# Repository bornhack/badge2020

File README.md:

# Bornhack Badge 2020

## About the hardware

Similar to the last couple of years, this badge has an ARM cortex M0+ as the main
controller, but on this badge it's the SAMD21 from Microchip, with 4 times as much
flash and RAM compared to the chips from the previous badges.

This makes it possible to run Adafruit CircuitPython on this badge, which lowers the
bar for how easy it is to get started hacking on the badge, since all you need is a
USB cable to connect it to your computer and an editor (vi, nano, VSCode, notepad,
you name it) to change the `code.py` file on the badge. No need to have a tool chain
installed on your computer, it's all happening on the badge when you save the file.

## Features

- The main feature of the badge is a 9x32 pixel LED matrix controlled by 2
IS31FL3731 LED controllers, that control the LEDs via charlieplexing
- The other primary feature is an infrared LED to transmit and an infrared receiver
and decoder to receive badge to badge communication
- There are also 4 navigation/game buttons and a reset button
- The badge is either powered by 2xAA batteries, that have the voltage boosted to
3.3v or via USB, where the voltage is regulated down to 3.3v
- The main controller is a SAMD21G18A with a GD25Q32C (4MB SPI flash) connected
for libraries, graphics, etc.
- There is also an unpopulated header for Shitty Add On v.1.69bis
- On the back of the badge, all i/o pins that are not used on the microcontroller
is pull out to small SMD pads for optional soldering on add-ons or similar.

## Getting started

To start making your badge your own, you can connect it via USB and a mass storage
device should show up with a `code.py` file in the root directory.

If you open that file in your favorite text editor you will find a few lines first
that loads some libraries, then some initialisation of the LED drivers and on line 20
you will find an assignment of a string variable with the scrolling text shown on
the LED matrix. To put eg. your name on the badge, you can change this text and save
the file, and after a few seconds, the badge will restart the code and your text
should be slowly scrolling across the "screen".

If you have gotten this far you are up and running with your first "hack" of the
2020 BornHack badge and you can continue with more elaborate hacking.

## Projects using the badge

- [Generative animations in OCaml](https://github.com/rand00/bornhack2020-badge_generative-animations)
  - Animations are pregenerated in OCaml and played back on the badge using python

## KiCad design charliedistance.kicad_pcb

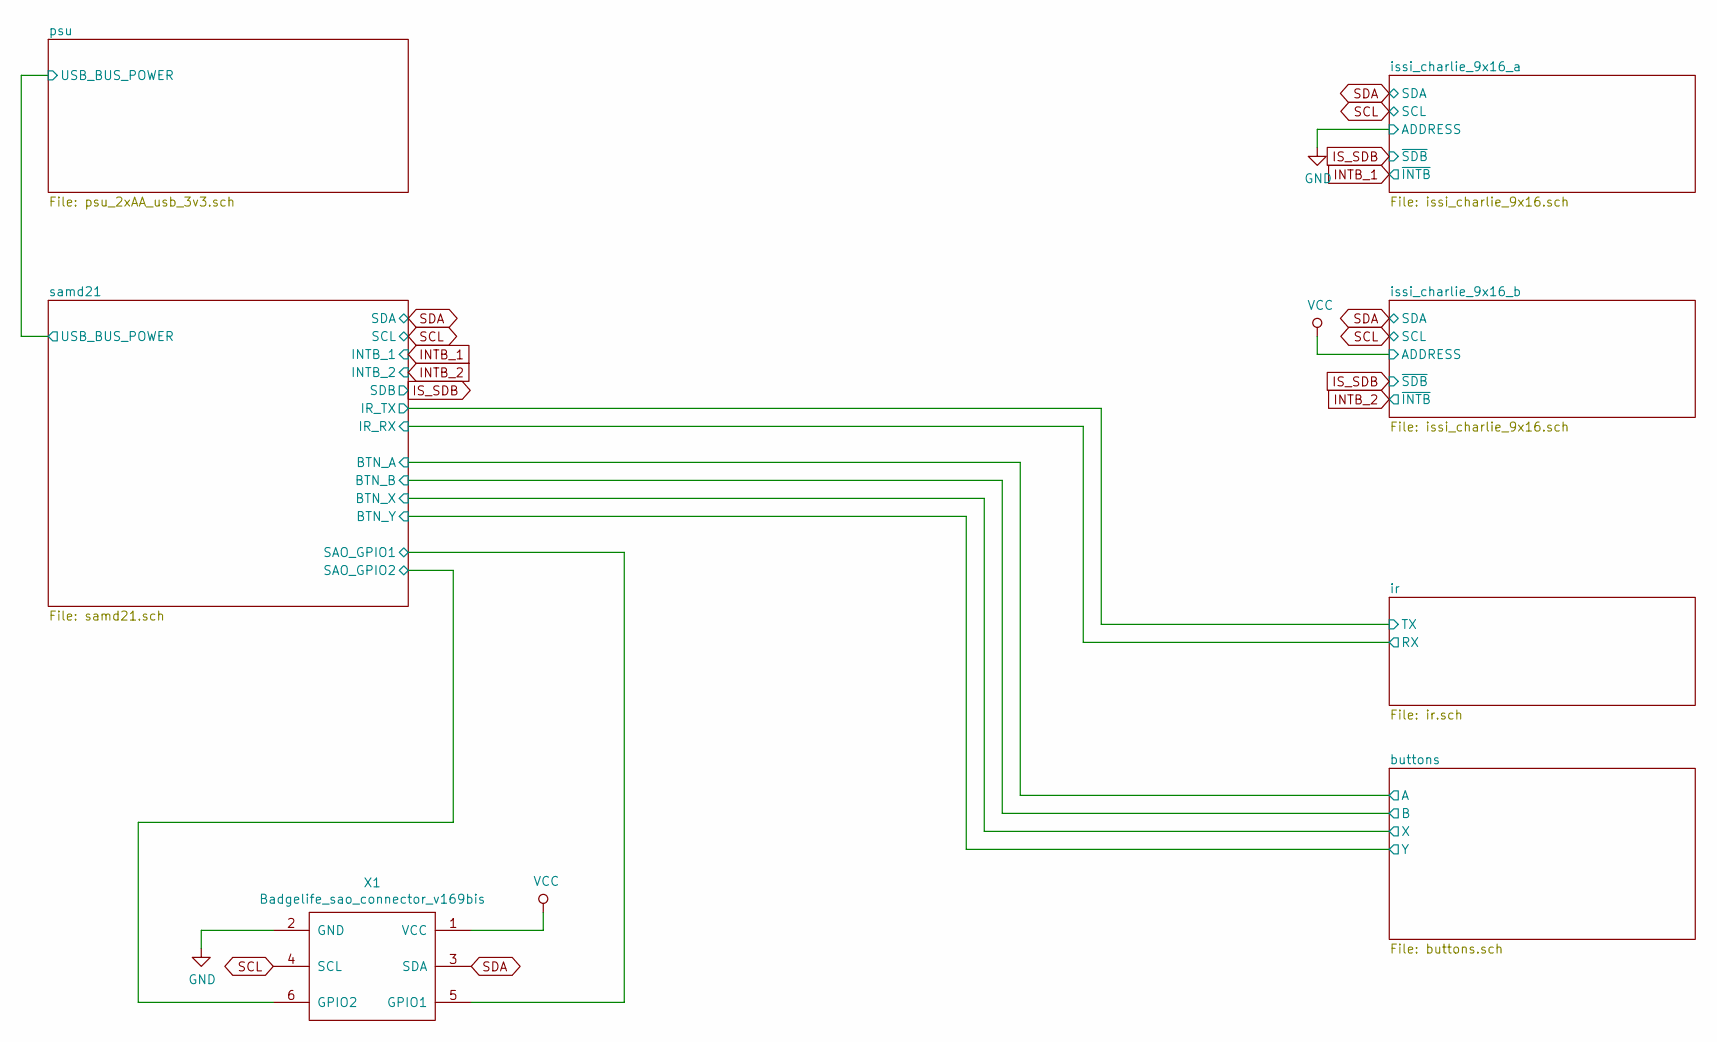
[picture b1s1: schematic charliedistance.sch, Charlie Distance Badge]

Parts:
X1: Badgelife_sao_connector_v169bis; Badgelife-SAOv169-BADGE-2x3

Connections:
/samd21/SAO_GPIO1: X1.5 (GPIO1); also elsewhere on the board
/samd21/SAO_GPIO2: X1.6 (GPIO2); also elsewhere on the board
GND: X1.2 (GND); also elsewhere on the board
SCL: X1.4 (SCL); also elsewhere on the board
SDA: X1.3 (SDA); also elsewhere on the board
VCC: X1.1 (VCC); also elsewhere on the board

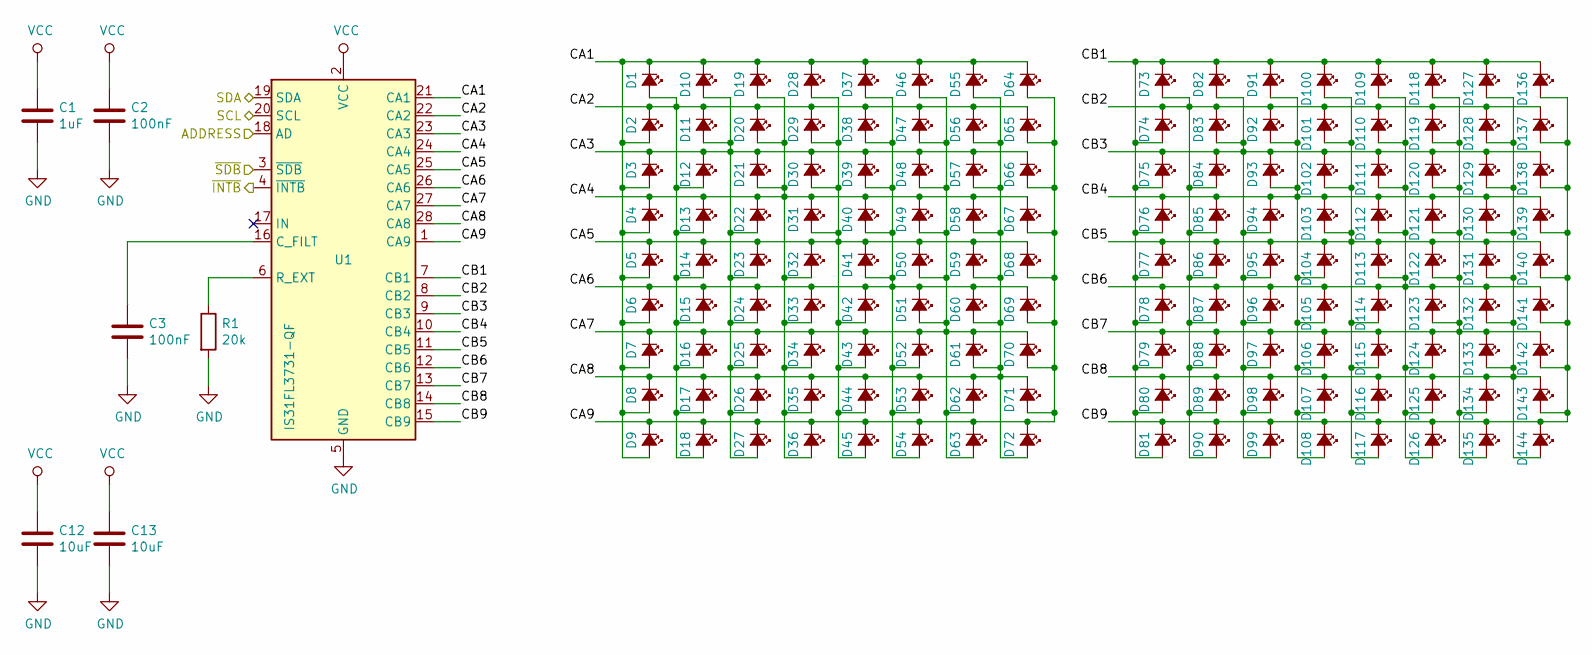
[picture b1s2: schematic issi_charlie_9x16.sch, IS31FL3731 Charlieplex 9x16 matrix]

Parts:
C1: 1uF; C_0603
C2, C3: 100nF; C_0603
C12, C13: 10uF; C_0603
D1, D2, D3, D4, D5, D6, D7, D8, D9, D10, D11, D12, D13, D14, D15, D16, D17, D18, D19, D20, D21, D22, D23, D24, D25, D26, D27, D28, D29, D30, D31, D32, D33, D34, D35, D36, D37, D38, D39, D40, D41, D42, D43, D44, D45, D46, D47, D48, D49, D50, D51, D52, D53, D54, D55, D56, D57, D58, D59, D60, D61, D62, D63, D64, D65, D66, D67, D68, D69, D70, D71, D72, D73, D74, D75, D76, D77, D78, D79, D80, D81, D82, D83, D84, D85, D86, D87, D88, D89, D90, D91, D92, D93, D94, D95, D96, D97, D98, D99, D100, D101, D102, D103, D104, D105, D106, D107, D108, D109, D110, D111, D112, D113, D114, D115, D116, D117, D118, D119, D120, D121, D122, D123, D124, D125, D126, D127, D128, D129, D130, D131, D132, D133, D134, D135, D136, D137, D138, D139, D140, D141, D142, D143, D144: LED_Small_ALT; LED_0603
R1: 20k; R_0603
U1: IS31FL3731-QF; QFN-28-1EP_4x4mm_Pitch0.4mm

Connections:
/issi_charlie_9x16_a/CA1: D1.1 (K), D2.2 (A), D3.2 (A), D4.2 (A), D5.2 (A), D6.2 (A), D7.2 (A), D8.2 (A), D9.2 (A), D10.1 (K), D19.1 (K), D28.1 (K), D37.1 (K), D46.1 (K), D55.1 (K), D64.1 (K), U1.21 (CA1)
/issi_charlie_9x16_a/CA2: D1.2 (A), D2.1 (K), D11.1 (K), D12.2 (A), D13.2 (A), D14.2 (A), D15.2 (A), D16.2 (A), D17.2 (A), D18.2 (A), D20.1 (K), D29.1 (K), D38.1 (K), D47.1 (K), D56.1 (K), D65.1 (K), U1.22 (CA2)
/issi_charlie_9x16_a/CA3: D3.1 (K), D10.2 (A), D11.2 (A), D12.1 (K), D21.1 (K), D22.2 (A), D23.2 (A), D24.2 (A), D25.2 (A), D26.2 (A), D27.2 (A), D30.1 (K), D39.1 (K), D48.1 (K), D57.1 (K), D66.1 (K), U1.23 (CA3)
/issi_charlie_9x16_a/CA4: D4.1 (K), D13.1 (K), D19.2 (A), D20.2 (A), D21.2 (A), D22.1 (K), D31.1 (K), D32.2 (A), D33.2 (A), D34.2 (A), D35.2 (A), D36.2 (A), D40.1 (K), D49.1 (K), D58.1 (K), D67.1 (K), U1.24 (CA4)
/issi_charlie_9x16_a/CA5: D5.1 (K), D14.1 (K), D23.1 (K), D28.2 (A), D29.2 (A), D30.2 (A), D31.2 (A), D32.1 (K), D41.1 (K), D42.2 (A), D43.2 (A), D44.2 (A), D45.2 (A), D50.1 (K), D59.1 (K), D68.1 (K), U1.25 (CA5)
/issi_charlie_9x16_a/CA6: D6.1 (K), D15.1 (K), D24.1 (K), D33.1 (K), D37.2 (A), D38.2 (A), D39.2 (A), D40.2 (A), D41.2 (A), D42.1 (K), D51.1 (K), D52.2 (A), D53.2 (A), D54.2 (A), D60.1 (K), D69.1 (K), U1.26 (CA6)
/issi_charlie_9x16_a/CA7: D7.1 (K), D16.1 (K), D25.1 (K), D34.1 (K), D43.1 (K), D46.2 (A), D47.2 (A), D48.2 (A), D49.2 (A), D50.2 (A), D51.2 (A), D52.1 (K), D61.1 (K), D62.2 (A), D63.2 (A), D70.1 (K), U1.27 (CA7)
/issi_charlie_9x16_a/CA8: D8.1 (K), D17.1 (K), D26.1 (K), D35.1 (K), D44.1 (K), D53.1 (K), D55.2 (A), D56.2 (A), D57.2 (A), D58.2 (A), D59.2 (A), D60.2 (A), D61.2 (A), D62.1 (K), D71.1 (K), D72.2 (A), U1.28 (CA8)
/issi_charlie_9x16_a/CA9: D9.1 (K), D18.1 (K), D27.1 (K), D36.1 (K), D45.1 (K), D54.1 (K), D63.1 (K), D64.2 (A), D65.2 (A), D66.2 (A), D67.2 (A), D68.2 (A), D69.2 (A), D70.2 (A), D71.2 (A), D72.1 (K), U1.1 (CA9)
/issi_charlie_9x16_a/CB1: D73.1 (K), D74.2 (A), D75.2 (A), D76.2 (A), D77.2 (A), D78.2 (A), D79.2 (A), D80.2 (A), D81.2 (A), D82.1 (K), D91.1 (K), D100.1 (K), D109.1 (K), D118.1 (K), D127.1 (K), D136.1 (K), U1.7 (CB1)
/issi_charlie_9x16_a/CB2: D73.2 (A), D74.1 (K), D83.1 (K), D84.2 (A), D85.2 (A), D86.2 (A), D87.2 (A), D88.2 (A), D89.2 (A), D90.2 (A), D92.1 (K), D101.1 (K), D110.1 (K), D119.1 (K), D128.1 (K), D137.1 (K), U1.8 (CB2)
/issi_charlie_9x16_a/CB3: D75.1 (K), D82.2 (A), D83.2 (A), D84.1 (K), D93.1 (K), D94.2 (A), D95.2 (A), D96.2 (A), D97.2 (A), D98.2 (A), D99.2 (A), D102.1 (K), D111.1 (K), D120.1 (K), D129.1 (K), D138.1 (K), U1.9 (CB3)
/issi_charlie_9x16_a/CB4: D76.1 (K), D85.1 (K), D91.2 (A), D92.2 (A), D93.2 (A), D94.1 (K), D103.1 (K), D104.2 (A), D105.2 (A), D106.2 (A), D107.2 (A), D108.2 (A), D112.1 (K), D121.1 (K), D130.1 (K), D139.1 (K), U1.10 (CB4)
/issi_charlie_9x16_a/CB5: D77.1 (K), D86.1 (K), D95.1 (K), D100.2 (A), D101.2 (A), D102.2 (A), D103.2 (A), D104.1 (K), D113.1 (K), D114.2 (A), D115.2 (A), D116.2 (A), D117.2 (A), D122.1 (K), D131.1 (K), D140.1 (K), U1.11 (CB5)
/issi_charlie_9x16_a/CB6: D78.1 (K), D87.1 (K), D96.1 (K), D105.1 (K), D109.2 (A), D110.2 (A), D111.2 (A), D112.2 (A), D113.2 (A), D114.1 (K), D123.1 (K), D124.2 (A), D125.2 (A), D126.2 (A), D132.1 (K), D141.1 (K), U1.12 (CB6)
/issi_charlie_9x16_a/CB7: D79.1 (K), D88.1 (K), D97.1 (K), D106.1 (K), D115.1 (K), D118.2 (A), D119.2 (A), D120.2 (A), D121.2 (A), D122.2 (A), D123.2 (A), D124.1 (K), D133.1 (K), D134.2 (A), D135.2 (A), D142.1 (K), U1.13 (CB7)
/issi_charlie_9x16_a/CB8: D80.1 (K), D89.1 (K), D98.1 (K), D107.1 (K), D116.1 (K), D125.1 (K), D127.2 (A), D128.2 (A), D129.2 (A), D130.2 (A), D131.2 (A), D132.2 (A), D133.2 (A), D134.1 (K), D143.1 (K), D144.2 (A), U1.14 (CB8)
/issi_charlie_9x16_a/CB9: D81.1 (K), D90.1 (K), D99.1 (K), D108.1 (K), D117.1 (K), D126.1 (K), D135.1 (K), D136.2 (A), D137.2 (A), D138.2 (A), D139.2 (A), D140.2 (A), D141.2 (A), D142.2 (A), D143.2 (A), D144.1 (K), U1.15 (CB9)
GND: C1.2, C2.2, C3.2, C12.2, C13.2, R1.2, U1.5 (GND), U1.18 (AD), U1.29 (GND); also elsewhere on the board
INTB_1: U1.4 (~INTB); also elsewhere on the board
IS_SDB: U1.3 (~SDB); also elsewhere on the board
unnamed: C3.1, U1.16 (C_FILT)
unnamed: R1.1, U1.6 (R_EXT)
SCL: U1.20 (SCL); also elsewhere on the board
SDA: U1.19 (SDA); also elsewhere on the board
VCC: C1.1, C2.1, C12.1, C13.1, U1.2 (VCC); also elsewhere on the board

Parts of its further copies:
C4: 1uF; C_0603
C5, C6: 100nF; C_0603
C14, C15: 10uF; C_0603
D145, D146, D147, D148, D149, D150, D151, D152, D153, D154, D155, D156, D157, D158, D159, D160, D161, D162, D163, D164, D165, D166, D167, D168, D169, D170, D171, D172, D173, D174, D175, D176, D177, D178, D179, D180, D181, D182, D183, D184, D185, D186, D187, D188, D189, D190, D191, D192, D193, D194, D195, D196, D197, D198, D199, D200, D201, D202, D203, D204, D205, D206, D207, D208, D209, D210, D211, D212, D213, D214, D215, D216, D217, D218, D219, D220, D221, D222, D223, D224, D225, D226, D227, D228, D229, D230, D231, D232, D233, D234, D235, D236, D237, D238, D239, D240, D241, D242, D243, D244, D245, D246, D247, D248, D249, D250, D251, D252, D253, D254, D255, D256, D257, D258, D259, D260, D261, D262, D263, D264, D265, D266, D267, D268, D269, D270, D271, D272, D273, D274, D275, D276, D277, D278, D279, D280, D281, D282, D283, D284, D285, D286, D287, D288: LED_Small_ALT; LED_0603
R2: 20k; R_0603
U2: IS31FL3731-QF; QFN-28-1EP_4x4mm_Pitch0.4mm

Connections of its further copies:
/issi_charlie_9x16_b/CA1: D145.1 (K), D146.2 (A), D147.2 (A), D148.2 (A), D149.2 (A), D150.2 (A), D151.2 (A), D152.2 (A), D153.2 (A), D154.1 (K), D163.1 (K), D172.1 (K), D181.1 (K), D190.1 (K), D199.1 (K), D208.1 (K), U2.21 (CA1)
/issi_charlie_9x16_b/CA2: D145.2 (A), D146.1 (K), D155.1 (K), D156.2 (A), D157.2 (A), D158.2 (A), D159.2 (A), D160.2 (A), D161.2 (A), D162.2 (A), D164.1 (K), D173.1 (K), D182.1 (K), D191.1 (K), D200.1 (K), D209.1 (K), U2.22 (CA2)
/issi_charlie_9x16_b/CA3: D147.1 (K), D154.2 (A), D155.2 (A), D156.1 (K), D165.1 (K), D166.2 (A), D167.2 (A), D168.2 (A), D169.2 (A), D170.2 (A), D171.2 (A), D174.1 (K), D183.1 (K), D192.1 (K), D201.1 (K), D210.1 (K), U2.23 (CA3)
/issi_charlie_9x16_b/CA4: D148.1 (K), D157.1 (K), D163.2 (A), D164.2 (A), D165.2 (A), D166.1 (K), D175.1 (K), D176.2 (A), D177.2 (A), D178.2 (A), D179.2 (A), D180.2 (A), D184.1 (K), D193.1 (K), D202.1 (K), D211.1 (K), U2.24 (CA4)
/issi_charlie_9x16_b/CA5: D149.1 (K), D158.1 (K), D167.1 (K), D172.2 (A), D173.2 (A), D174.2 (A), D175.2 (A), D176.1 (K), D185.1 (K), D186.2 (A), D187.2 (A), D188.2 (A), D189.2 (A), D194.1 (K), D203.1 (K), D212.1 (K), U2.25 (CA5)
/issi_charlie_9x16_b/CA6: D150.1 (K), D159.1 (K), D168.1 (K), D177.1 (K), D181.2 (A), D182.2 (A), D183.2 (A), D184.2 (A), D185.2 (A), D186.1 (K), D195.1 (K), D196.2 (A), D197.2 (A), D198.2 (A), D204.1 (K), D213.1 (K), U2.26 (CA6)
/issi_charlie_9x16_b/CA7: D151.1 (K), D160.1 (K), D169.1 (K), D178.1 (K), D187.1 (K), D190.2 (A), D191.2 (A), D192.2 (A), D193.2 (A), D194.2 (A), D195.2 (A), D196.1 (K), D205.1 (K), D206.2 (A), D207.2 (A), D214.1 (K), U2.27 (CA7)
/issi_charlie_9x16_b/CA8: D152.1 (K), D161.1 (K), D170.1 (K), D179.1 (K), D188.1 (K), D197.1 (K), D199.2 (A), D200.2 (A), D201.2 (A), D202.2 (A), D203.2 (A), D204.2 (A), D205.2 (A), D206.1 (K), D215.1 (K), D216.2 (A), U2.28 (CA8)
/issi_charlie_9x16_b/CA9: D153.1 (K), D162.1 (K), D171.1 (K), D180.1 (K), D189.1 (K), D198.1 (K), D207.1 (K), D208.2 (A), D209.2 (A), D210.2 (A), D211.2 (A), D212.2 (A), D213.2 (A), D214.2 (A), D215.2 (A), D216.1 (K), U2.1 (CA9)
/issi_charlie_9x16_b/CB1: D217.1 (K), D218.2 (A), D219.2 (A), D220.2 (A), D221.2 (A), D222.2 (A), D223.2 (A), D224.2 (A), D225.2 (A), D226.1 (K), D235.1 (K), D244.1 (K), D253.1 (K), D262.1 (K), D271.1 (K), D280.1 (K), U2.7 (CB1)
/issi_charlie_9x16_b/CB2: D217.2 (A), D218.1 (K), D227.1 (K), D228.2 (A), D229.2 (A), D230.2 (A), D231.2 (A), D232.2 (A), D233.2 (A), D234.2 (A), D236.1 (K), D245.1 (K), D254.1 (K), D263.1 (K), D272.1 (K), D281.1 (K), U2.8 (CB2)
/issi_charlie_9x16_b/CB3: D219.1 (K), D226.2 (A), D227.2 (A), D228.1 (K), D237.1 (K), D238.2 (A), D239.2 (A), D240.2 (A), D241.2 (A), D242.2 (A), D243.2 (A), D246.1 (K), D255.1 (K), D264.1 (K), D273.1 (K), D282.1 (K), U2.9 (CB3)
/issi_charlie_9x16_b/CB4: D220.1 (K), D229.1 (K), D235.2 (A), D236.2 (A), D237.2 (A), D238.1 (K), D247.1 (K), D248.2 (A), D249.2 (A), D250.2 (A), D251.2 (A), D252.2 (A), D256.1 (K), D265.1 (K), D274.1 (K), D283.1 (K), U2.10 (CB4)
/issi_charlie_9x16_b/CB5: D221.1 (K), D230.1 (K), D239.1 (K), D244.2 (A), D245.2 (A), D246.2 (A), D247.2 (A), D248.1 (K), D257.1 (K), D258.2 (A), D259.2 (A), D260.2 (A), D261.2 (A), D266.1 (K), D275.1 (K), D284.1 (K), U2.11 (CB5)
/issi_charlie_9x16_b/CB6: D222.1 (K), D231.1 (K), D240.1 (K), D249.1 (K), D253.2 (A), D254.2 (A), D255.2 (A), D256.2 (A), D257.2 (A), D258.1 (K), D267.1 (K), D268.2 (A), D269.2 (A), D270.2 (A), D276.1 (K), D285.1 (K), U2.12 (CB6)
/issi_charlie_9x16_b/CB7: D223.1 (K), D232.1 (K), D241.1 (K), D250.1 (K), D259.1 (K), D262.2 (A), D263.2 (A), D264.2 (A), D265.2 (A), D266.2 (A), D267.2 (A), D268.1 (K), D277.1 (K), D278.2 (A), D279.2 (A), D286.1 (K), U2.13 (CB7)
/issi_charlie_9x16_b/CB8: D224.1 (K), D233.1 (K), D242.1 (K), D251.1 (K), D260.1 (K), D269.1 (K), D271.2 (A), D272.2 (A), D273.2 (A), D274.2 (A), D275.2 (A), D276.2 (A), D277.2 (A), D278.1 (K), D287.1 (K), D288.2 (A), U2.14 (CB8)
/issi_charlie_9x16_b/CB9: D225.1 (K), D234.1 (K), D243.1 (K), D252.1 (K), D261.1 (K), D270.1 (K), D279.1 (K), D280.2 (A), D281.2 (A), D282.2 (A), D283.2 (A), D284.2 (A), D285.2 (A), D286.2 (A), D287.2 (A), D288.1 (K), U2.15 (CB9)
GND: C4.2, C5.2, C6.2, C14.2, C15.2, R2.2, U2.5 (GND), U2.29 (GND); also elsewhere on the board
INTB_2: U2.4 (~INTB); also elsewhere on the board
IS_SDB: U2.3 (~SDB); also elsewhere on the board
unnamed: C6.1, U2.16 (C_FILT)
unnamed: R2.1, U2.6 (R_EXT)
SCL: U2.20 (SCL); also elsewhere on the board
SDA: U2.19 (SDA); also elsewhere on the board
VCC: C4.1, C5.1, C14.1, C15.1, U2.2 (VCC), U2.18 (AD); also elsewhere on the board

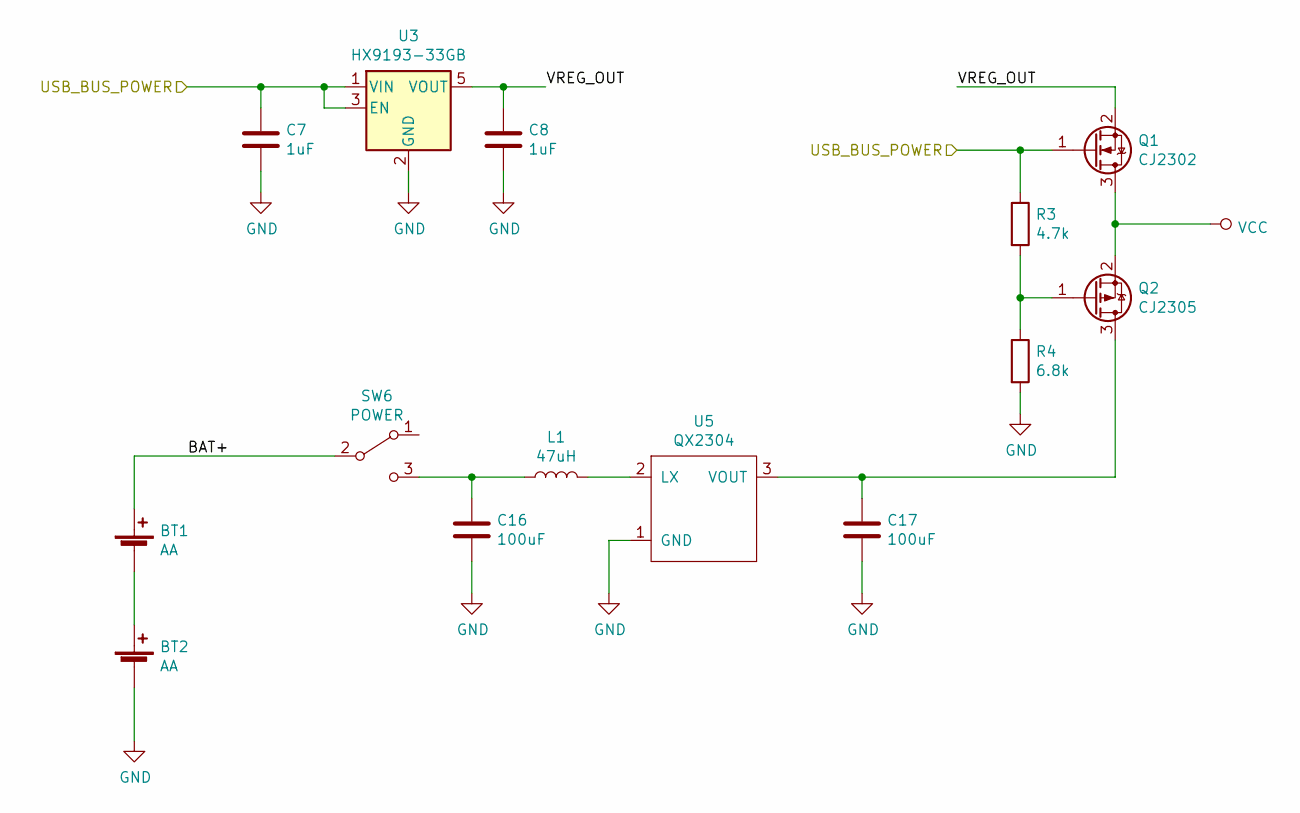
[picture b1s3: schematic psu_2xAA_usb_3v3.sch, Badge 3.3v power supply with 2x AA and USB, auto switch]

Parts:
BT1, BT2: AA; Single_AA
C7, C8: 1uF; C_0603
C16, C17: 100uF; C_1206
L1: 47uH; L_1210
Q1: CJ2302; SOT-23
Q2: CJ2305; SOT-23
R3: 4.7k; R_0603
R4: 6.8k; R_0603
SW6: POWER; SW_SPDT_PCM12
U3: HX9193-33GB; SOT-23-5
U5: QX2304; SOT-23

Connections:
/psu/BAT+: BT1.1 (+), SW6.2 (B)
/psu/USB_BUS_POWER: C7.1, Q1.1 (G), R3.1, U3.1 (VIN), U3.3 (EN); also elsewhere on the board
/psu/VREG_OUT: C8.1, Q1.2 (S), U3.5 (VOUT)
GND: BT2.2 (-), C7.2, C8.2, C16.2, C17.2, R4.2, U3.2 (GND), U5.1 (GND); also elsewhere on the board
unnamed: BT1.2 (-), BT2.1 (+)
unnamed: C16.1, L1.1, SW6.3 (C)
unnamed: C17.1, Q2.3 (D), U5.3 (VOUT)
unnamed: L1.2, U5.2 (LX)
unnamed: Q2.1 (G), R3.2, R4.1
VCC: Q1.3 (D), Q2.2 (S); also elsewhere on the board

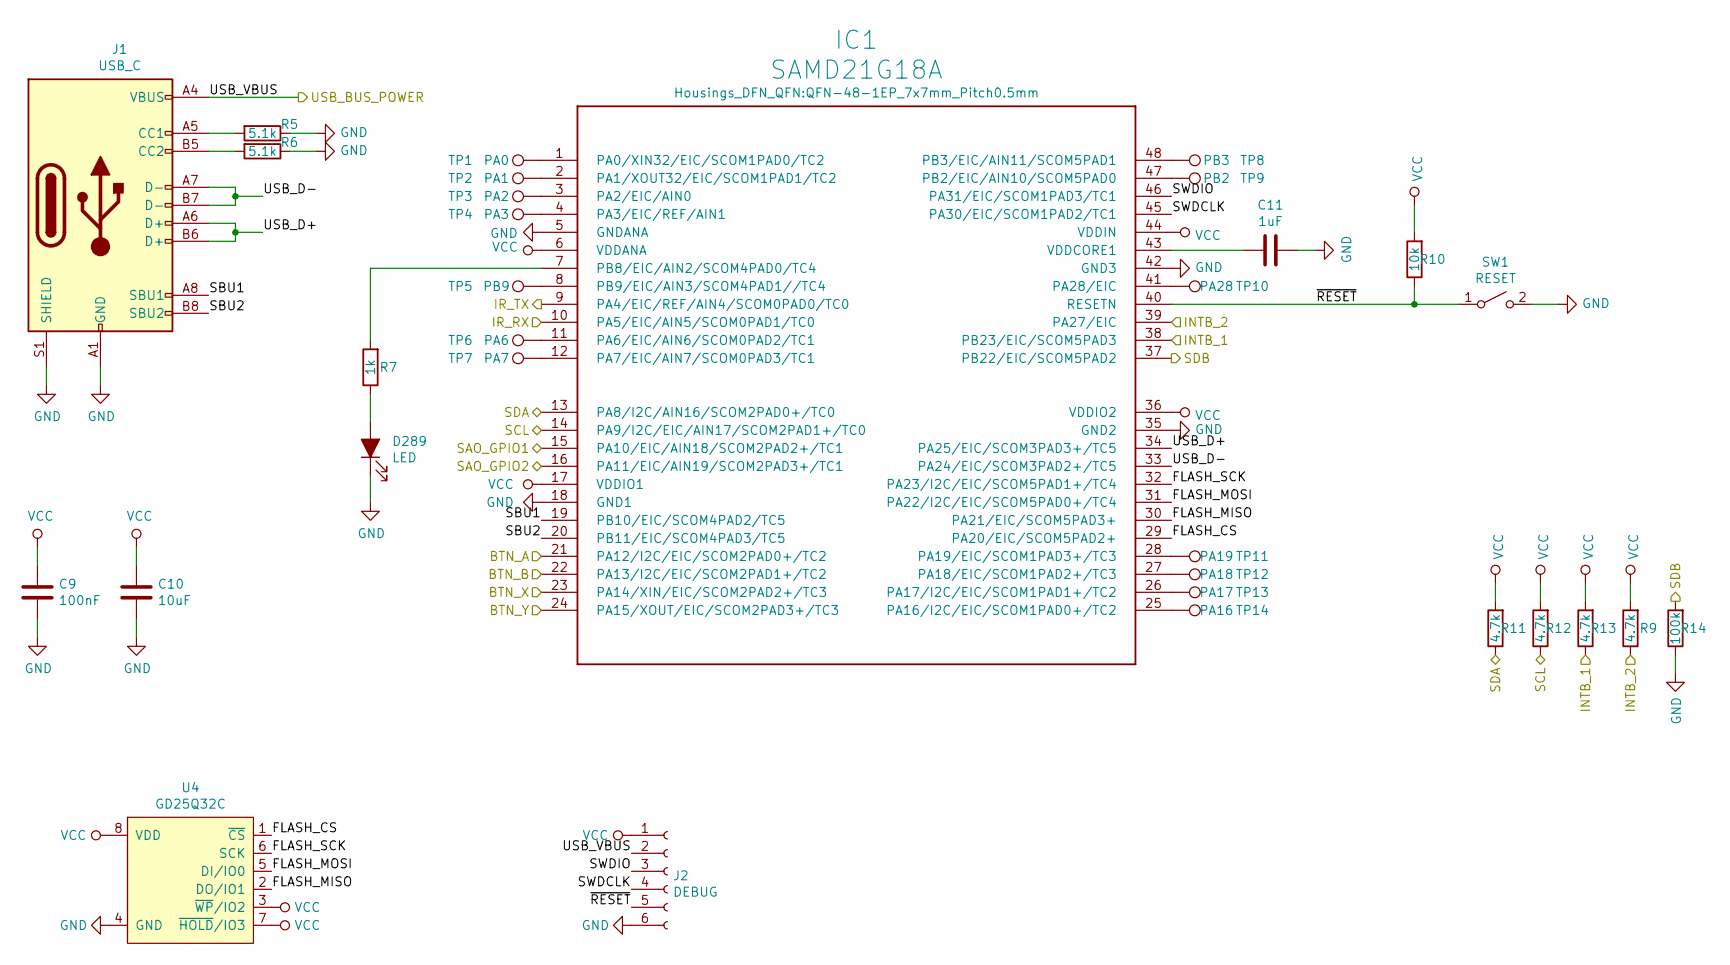
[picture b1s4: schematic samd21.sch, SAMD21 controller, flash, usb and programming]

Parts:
C9: 100nF; C_0603
C10: 10uF; C_0603
C11: 1uF; C_0603
D289: LED; LED_0603
IC1: SAMD21G18A; QFN-48-1EP_7x7mm_Pitch0.5mm
J1: USB_C; USB_C_Receptacle_U262-161N-4BVC11
J2: DEBUG; Pin_Header_Straight_1x06_Pitch2.54mm
R5, R6: 5.1k; R_0603
R7: 1k; R_0603
R9, R11, R12, R13: 4.7k; R_0603
R10: 10k; R_0603
R14: 100k; R_0603
SW1: RESET; SW_SPST_TL3342
TP1: PA0; TestPoint_Large
TP2: PA1; TestPoint_Large
TP3: PA2; TestPoint_Large
TP4: PA3; TestPoint_Large
TP5: PB9; TestPoint_Large
TP6: PA6; TestPoint_Large
TP7: PA7; TestPoint_Large
TP8: PB3; TestPoint_Large
TP9: PB2; TestPoint_Large
TP10: PA28; TestPoint_Large
TP11: PA19; TestPoint_Large
TP12: PA18; TestPoint_Large
TP13: PA17; TestPoint_Large
TP14: PA16; TestPoint_Large
U4: GD25Q32C; SOIC-8-1EP_3.9x4.9mm_Pitch1.27mm

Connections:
/buttons/A: IC1.21 (PA12/I2C/EIC/SCOM2PAD0+/TC2); also elsewhere on the board
/buttons/B: IC1.22 (PA13/I2C/EIC/SCOM2PAD1+/TC2); also elsewhere on the board
/psu/USB_BUS_POWER: J1.A4 (VBUS), J1.A9 (VBUS), J1.B4 (VBUS), J1.B9 (VBUS), J2.2; also elsewhere on the board
/samd21/BTN_X: IC1.23 (PA14/XIN/EIC/SCOM2PAD2+/TC3); also elsewhere on the board
/samd21/BTN_Y: IC1.24 (PA15/XOUT/EIC/SCOM2PAD3+/TC3); also elsewhere on the board
/samd21/FLASH_CS: IC1.29 (PA20/EIC/SCOM5PAD2+), U4.1 (~CS~)
/samd21/FLASH_MISO: IC1.30 (PA21/EIC/SCOM5PAD3+), U4.2 (DO/IO1)
/samd21/FLASH_MOSI: IC1.31 (PA22/I2C/EIC/SCOM5PAD0+/TC4), U4.5 (DI/IO0)
/samd21/FLASH_SCK: IC1.32 (PA23/I2C/EIC/SCOM5PAD1+/TC4), U4.6 (SCK)
/samd21/IR_RX: IC1.10 (PA5/EIC/AIN5/SCOM0PAD1/TC0); also elsewhere on the board
/samd21/IR_TX: IC1.9 (PA4/EIC/REF/AIN4/SCOM0PAD0/TC0); also elsewhere on the board
/samd21/SAO_GPIO1: IC1.15 (PA10/EIC/AIN18/SCOM2PAD2+/TC1); also elsewhere on the board
/samd21/SAO_GPIO2: IC1.16 (PA11/EIC/AIN19/SCOM2PAD3+/TC1); also elsewhere on the board
/samd21/SBU1: IC1.19 (PB10/EIC/SCOM4PAD2/TC5), J1.A8 (SBU1)
/samd21/SBU2: IC1.20 (PB11/EIC/SCOM4PAD3/TC5), J1.B8 (SBU2)
/samd21/SWDCLK: IC1.45 (PA30/EIC/SCOM1PAD2/TC1), J2.4
/samd21/SWDIO: IC1.46 (PA31/EIC/SCOM1PAD3/TC1), J2.3
/samd21/USB_D+: IC1.34 (PA25/EIC/SCOM3PAD3+/TC5), J1.A6 (D+), J1.B6 (D+)
/samd21/USB_D-: IC1.33 (PA24/EIC/SCOM3PAD2+/TC5), J1.A7 (D-), J1.B7 (D-)
/samd21/~RESET: IC1.40 (RESETN), J2.5, R10.1, SW1.1 (A)
GND: C9.2, C10.2, C11.2, D289.1 (K), IC1.5 (GNDANA), IC1.18 (GND1), IC1.35 (GND2), IC1.42 (GND3), J1.A1 (GND), J1.A12 (GND), J1.B1 (GND), J1.B12 (GND), J1.S1 (SHIELD), J2.6, R5.1, R6.1, R14.1, SW1.2 (B), U4.4 (GND); also elsewhere on the board
INTB_1: IC1.38 (PB23/EIC/SCOM5PAD3), R13.1; also elsewhere on the board
INTB_2: IC1.39 (PA27/EIC), R9.1; also elsewhere on the board
IS_SDB: IC1.37 (PB22/EIC/SCOM5PAD2), R14.2; also elsewhere on the board
unnamed: C11.1, IC1.43 (VDDCORE1)
unnamed: D289.2 (A), R7.1
unnamed: IC1.1 (PA0/XIN32/EIC/SCOM1PAD0/TC2), TP1.1
unnamed: IC1.2 (PA1/XOUT32/EIC/SCOM1PAD1/TC2), TP2.1
unnamed: IC1.3 (PA2/EIC/AIN0), TP3.1
unnamed: IC1.4 (PA3/EIC/REF/AIN1), TP4.1
unnamed: IC1.7 (PB8/EIC/AIN2/SCOM4PAD0/TC4), R7.2
unnamed: IC1.8 (PB9/EIC/AIN3/SCOM4PAD1//TC4), TP5.1
unnamed: IC1.11 (PA6/EIC/AIN6/SCOM0PAD2/TC1), TP6.1
unnamed: IC1.12 (PA7/EIC/AIN7/SCOM0PAD3/TC1), TP7.1
unnamed: IC1.25 (PA16/I2C/EIC/SCOM1PAD0+/TC2), TP14.1
unnamed: IC1.26 (PA17/I2C/EIC/SCOM1PAD1+/TC2), TP13.1
unnamed: IC1.27 (PA18/EIC/SCOM1PAD2+/TC3), TP12.1
unnamed: IC1.28 (PA19/EIC/SCOM1PAD3+/TC3), TP11.1
unnamed: IC1.41 (PA28/EIC), TP10.1
unnamed: IC1.47 (PB2/EIC/AIN10/SCOM5PAD0), TP9.1
unnamed: IC1.48 (PB3/EIC/AIN11/SCOM5PAD1), TP8.1
unnamed: J1.A5 (CC1), R5.2
unnamed: J1.B5 (CC2), R6.2
SCL: IC1.14 (PA9/I2C/EIC/AIN17/SCOM2PAD1+/TC0), R12.1; also elsewhere on the board
SDA: IC1.13 (PA8/I2C/AIN16/SCOM2PAD0+/TC0), R11.1; also elsewhere on the board
VCC: C9.1, C10.1, IC1.6 (VDDANA), IC1.17 (VDDIO1), IC1.36 (VDDIO2), IC1.44 (VDDIN), J2.1, R9.2, R10.2, R11.2, R12.2, R13.2, U4.3 (~WP~/IO2), U4.7 (~HOLD~/IO3), U4.8 (VDD); also elsewhere on the board

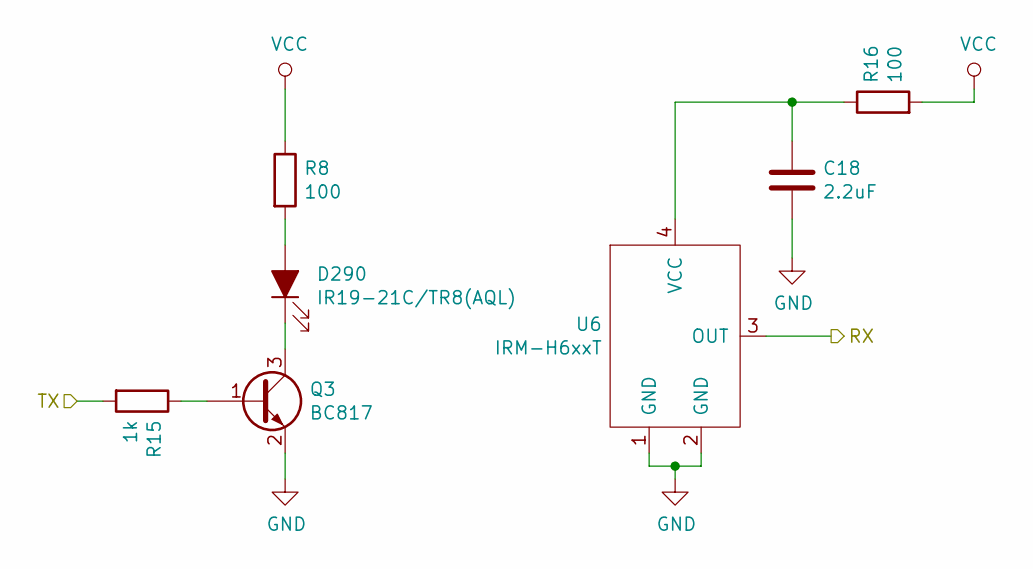
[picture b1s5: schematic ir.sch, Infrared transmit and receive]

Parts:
C18: 2.2uF; C_0603
D290: IR19-21C/TR8(AQL); LED_0603
Q3: BC817; SOT-23
R8, R16: 100; R_0603
R15: 1k; R_0603
U6: IRM-H6xxT

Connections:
/samd21/IR_RX: U6.3 (OUT); also elsewhere on the board
/samd21/IR_TX: R15.2; also elsewhere on the board
GND: C18.2, Q3.2 (E), U6.1 (GND), U6.2 (GND); also elsewhere on the board
unnamed: C18.1, R16.1, U6.4 (VCC)
unnamed: D290.1 (K), Q3.3 (C)
unnamed: D290.2 (A), R8.2
unnamed: Q3.1 (B), R15.1
VCC: R8.1, R16.2; also elsewhere on the board

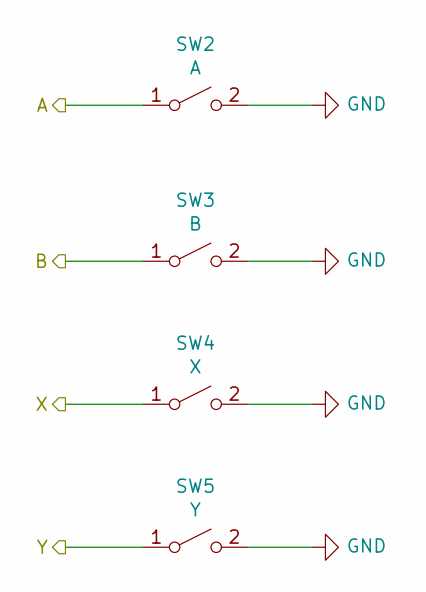
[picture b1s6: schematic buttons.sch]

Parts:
SW2: A; SW_SPST_TS3625A-HT
SW3: B; SW_SPST_TS3625A-HT
SW4: X; SW_SPST_TS3625A-HT
SW5: Y; SW_SPST_TS3625A-HT

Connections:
/buttons/A: SW2.1 (A); also elsewhere on the board
/buttons/B: SW3.1 (A); also elsewhere on the board
/samd21/BTN_X: SW4.1 (A); also elsewhere on the board
/samd21/BTN_Y: SW5.1 (A); also elsewhere on the board
GND: SW2.2 (B), SW3.2 (B), SW4.2 (B), SW5.2 (B); also elsewhere on the board

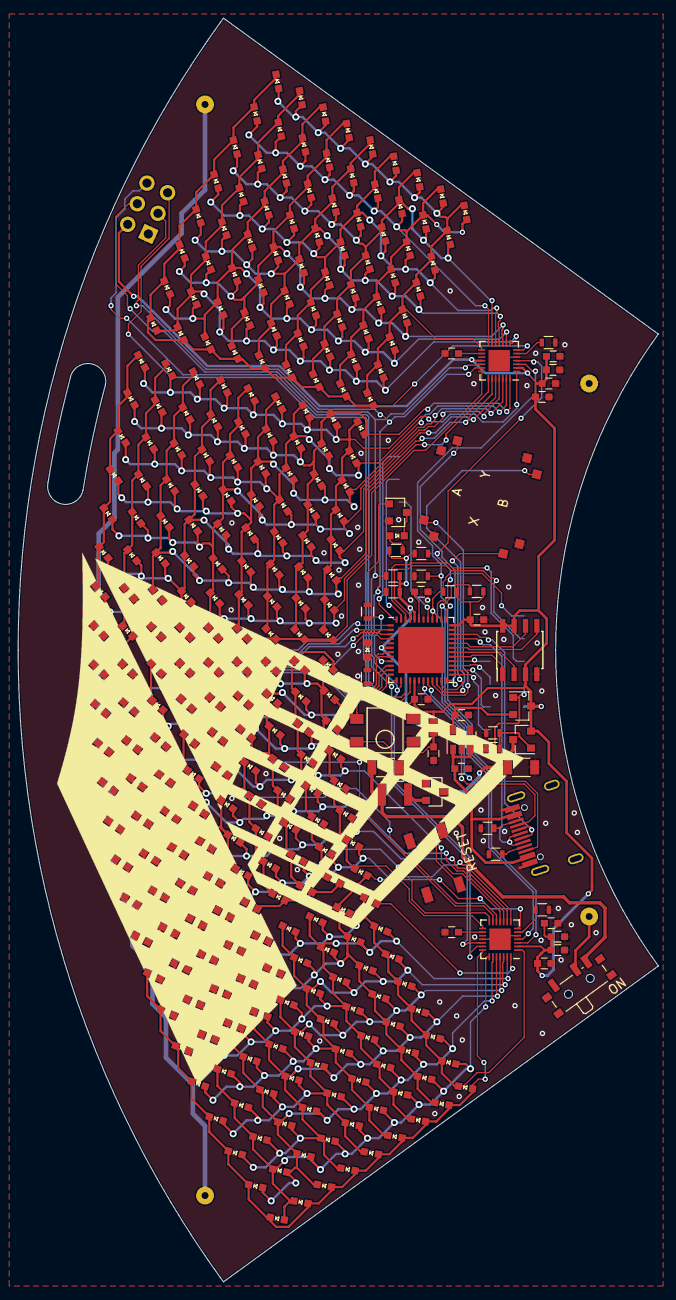
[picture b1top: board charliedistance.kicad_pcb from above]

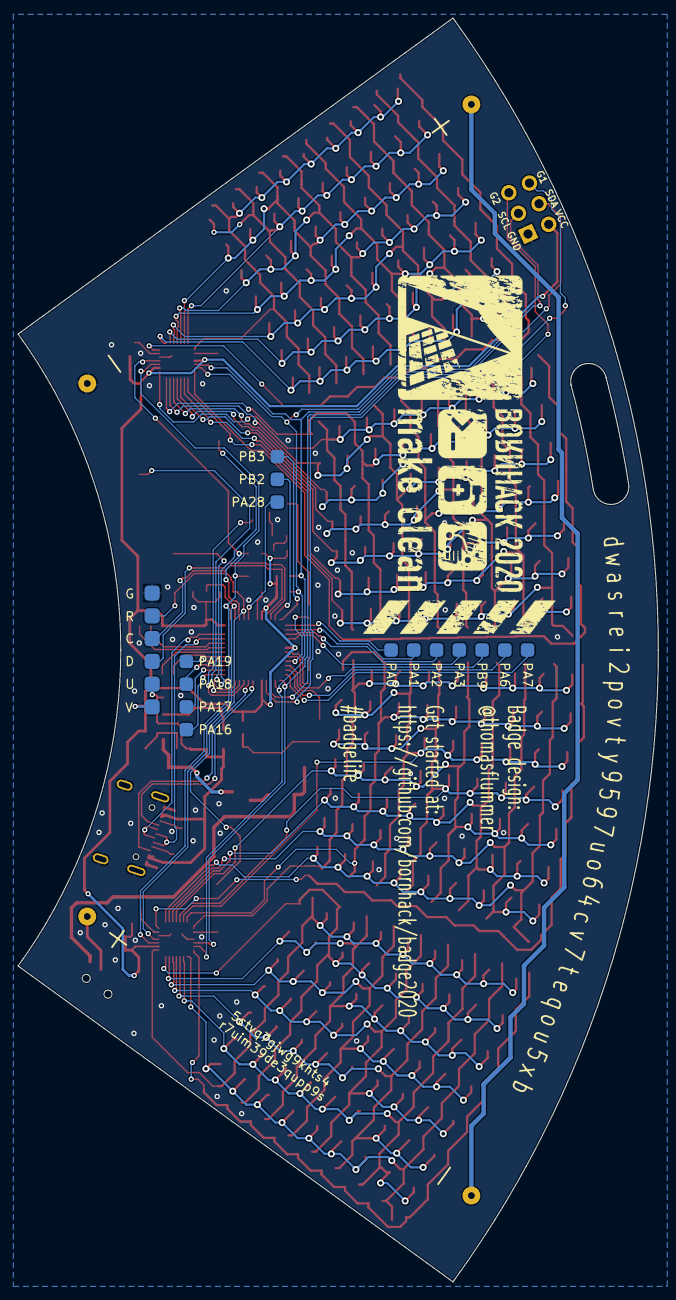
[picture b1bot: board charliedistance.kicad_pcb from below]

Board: 2 copper layers, 71.5 x 141.1 mm, 360 parts (17 on the bottom side), 97 nets.

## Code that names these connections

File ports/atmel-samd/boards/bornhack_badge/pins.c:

#include "shared-bindings/board/__init__.h"

STATIC const mp_rom_map_elem_t board_global_dict_table[] = {
    { MP_ROM_QSTR(MP_QSTR_RX), MP_ROM_PTR(&pin_PA05) },
    { MP_ROM_QSTR(MP_QSTR_TX), MP_ROM_PTR(&pin_PA04) },
    { MP_ROM_QSTR(MP_QSTR_SCK), MP_ROM_PTR(&pin_PA23) },
    { MP_ROM_QSTR(MP_QSTR_MOSI), MP_ROM_PTR(&pin_PA22) },
    { MP_ROM_QSTR(MP_QSTR_MISO), MP_ROM_PTR(&pin_PA21) },
    { MP_ROM_QSTR(MP_QSTR_SCL), MP_ROM_PTR(&pin_PA09) },
    { MP_ROM_QSTR(MP_QSTR_SDA), MP_ROM_PTR(&pin_PA08) },
    { MP_ROM_QSTR(MP_QSTR_LED),   MP_ROM_PTR(&pin_PB08) },
    { MP_ROM_QSTR(MP_QSTR_SBU1), MP_ROM_PTR(&pin_PB10) },
    { MP_ROM_QSTR(MP_QSTR_SBU2), MP_ROM_PTR(&pin_PB11) },
    { MP_ROM_QSTR(MP_QSTR_SAO1), MP_ROM_PTR(&pin_PA10) },
    { MP_ROM_QSTR(MP_QSTR_SAO2), MP_ROM_PTR(&pin_PA11) },
    { MP_ROM_QSTR(MP_QSTR_SDB), MP_ROM_PTR(&pin_PB22) },
    { MP_ROM_QSTR(MP_QSTR_INTB), MP_ROM_PTR(&pin_PB23) },
    { MP_ROM_QSTR(MP_QSTR_BTNA), MP_ROM_PTR(&pin_PA12) },
    { MP_ROM_QSTR(MP_QSTR_BTNB), MP_ROM_PTR(&pin_PA13) },
    { MP_ROM_QSTR(MP_QSTR_BTNX), MP_ROM_PTR(&pin_PA14) },
    { MP_ROM_QSTR(MP_QSTR_BTNY), MP_ROM_PTR(&pin_PA15) },
    { MP_ROM_QSTR(MP_QSTR_I2C), MP_ROM_PTR(&board_i2c_obj) },
    { MP_ROM_QSTR(MP_QSTR_SPI), MP_ROM_PTR(&board_spi_obj) },
    { MP_ROM_QSTR(MP_QSTR_UART), MP_ROM_PTR(&board_uart_obj) },
};
MP_DEFINE_CONST_DICT(board_module_globals, board_global_dict_table);

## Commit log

2020-08-12 Updates to production version
    Changed infrared setup, added step-up for battery power, added battery power switch, added more capacitors, changed and added logos, etc.
2020-08-12 Added license and readme
2020-08-12 add code example from badge
2020-08-12 Fix typo in readme
2020-08-12 Add example for buttons
2020-08-12 CYBER
2020-08-13 Add PDF version of the schematic
2020-08-13 Fixed formatting of buttons code example
2020-08-13 Added snake example code
2020-08-13 Fixed permission and a import error in the codee
2020-08-16 Added BornHack 2020 Badge
    Preliminary version
2020-08-21 README: Added link to 'Generative animations using OCaml' + new 'projects' section
2020-08-21 README: Renamed 'projects' title
2020-08-21 README: Added short description to 'generative animations in OCaml' projects-entry
